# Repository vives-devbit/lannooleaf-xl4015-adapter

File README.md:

# LannooLeaf Panel - XL4015 Adapter

| Front | Back |
|---|---|
|  |

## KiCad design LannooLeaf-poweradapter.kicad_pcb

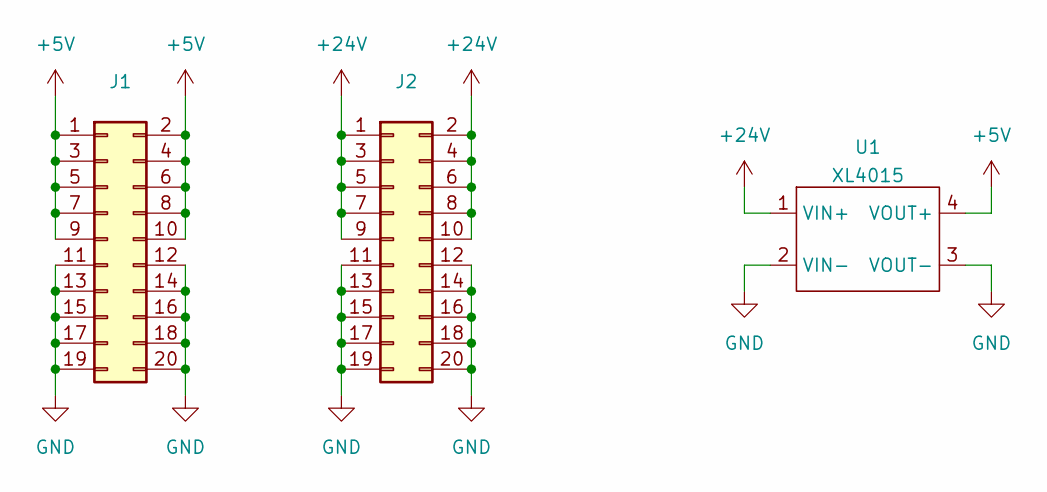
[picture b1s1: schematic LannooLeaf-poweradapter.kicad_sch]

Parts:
J1, J2: Conn_02x10_Counter_Clockwise; PinHeader_2x10_P2.54mm_Vertical
U1: XL4015

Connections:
+5V: J1.1, J1.2, J1.3, J1.4, J1.5, J1.6, J1.7, J1.8, J1.9, J1.10, U1.4 (VOUT+)
+24V: J2.1, J2.2, J2.3, J2.4, J2.5, J2.6, J2.7, J2.8, J2.9, J2.10, U1.1 (VIN+)
GND: J1.11, J1.12, J1.13, J1.14, J1.15, J1.16, J1.17, J1.18, J1.19, J1.20, J2.11, J2.12, J2.13, J2.14, J2.15, J2.16, J2.17, J2.18, J2.19, J2.20, U1.2 (VIN-), U1.3 (VOUT-)

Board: 2 copper layers, 7 parts (2 on the bottom side), 3 nets, no tracks yet.

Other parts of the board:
kibuzzard-62A851E8: G***; kibuzzard-62A851E8
kibuzzard-62A851F9: G***; kibuzzard-62A851F9
kibuzzard-62A8520A: G***; kibuzzard-62A8520A
kibuzzard-62A85210: G***; kibuzzard-62A85210

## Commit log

2022-06-14 v1.0
